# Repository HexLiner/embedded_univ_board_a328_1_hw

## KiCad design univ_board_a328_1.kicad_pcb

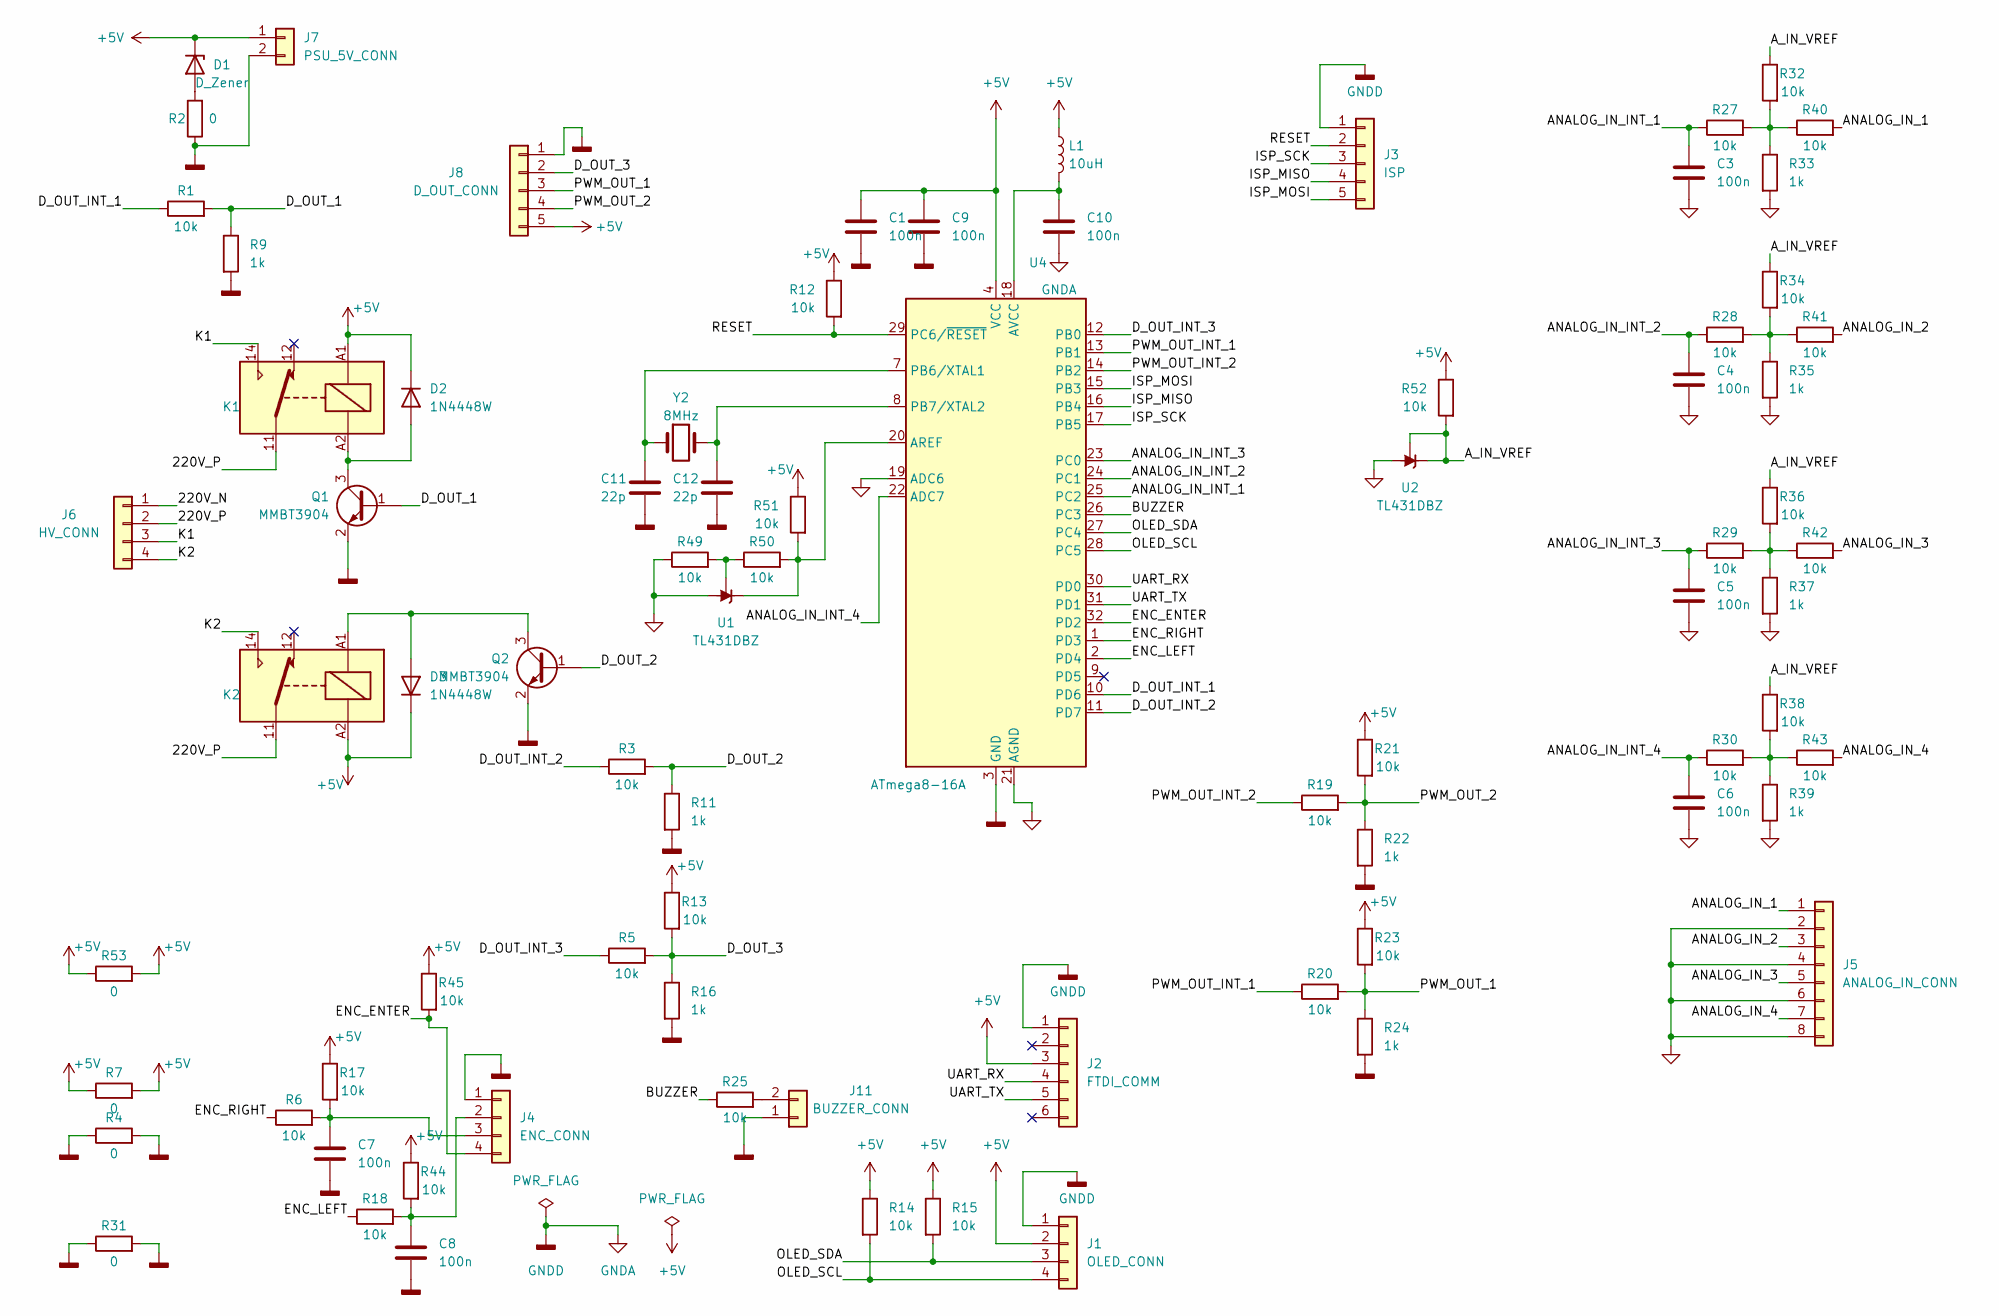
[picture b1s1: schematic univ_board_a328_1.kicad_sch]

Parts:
C1, C3, C4, C5, C6, C7, C8, C9, C10: 100n; C_0805_2012Metric
C11, C12: 22p; C_0603_1608Metric
D1: D_Zener; D_SOD-123
D2, D3: 1N4448W; D_SOD-123
J1: OLED_CONN; PinHeader_1x04_P2.54mm_Vertical
J2: FTDI_COMM; PinSocket_1x06_P2.54mm_Vertical
J3: ISP; PinSocket_1x05_P2.54mm_Vertical
J4: ENC_CONN; PinHeader_1x04_P2.54mm_Vertical
J5: ANALOG_IN_CONN; my_8pin_smd_conn
J6: HV_CONN; my_4pin_220v_conn
J7: PSU_5V_CONN; my_2pin_DIP_conn
J8: D_OUT_CONN; my_5pin_snd_conn
J11: BUZZER_CONN; PinHeader_1x02_P2.54mm_Vertical
K1, K2: FINDER-36.11; Relay_SPDT_Finder_36.11
L1: 10uH; L_0805_2012Metric
Q1, Q2: MMBT3904; SOT-23
R1, R3, R5, R6, R12, R14, R15, R18, R19, R20, R21, R25, R27, R28, R29, R30, R32, R34, R36, R38, R40, R41, R42, R43, R45, R49, R50, R51, R52: 10k; R_0805_2012Metric
R2, R4, R7, R31, R53: 0; R_1206_3216Metric
R9, R11, R16, R22, R24, R33, R35, R37, R39: 1k; R_0805_2012Metric
R13, R17, R23, R44: 10k; R_1206_3216Metric
U1, U2: TL431DBZ; SOT-23
U4: ATmega8-16A; TQFP-32_7x7mm_P0.8mm
Y2: 8MHz; Crystal_HC18-U_Vertical

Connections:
+5V: C1.1, C9.1, D1.1 (K), D2.1 (K), D3.1 (K), J1.2, J2.3, J7.1, J8.5, K1.A1, K2.A2, L1.1, R7.1, R7.2, R12.1, R13.1, R14.1, R15.1, R17.1, R21.1, R23.1, R44.1, R45.1, R51.1, R52.1, R53.1, R53.2, U4.4 (VCC), U4.6 (VCC)
/220V_N: J6.1
/220V_P: J6.2, K1.11, K2.11
/ANALOG_IN_1: J5.1, R40.2
/ANALOG_IN_2: J5.3, R41.2
/ANALOG_IN_3: J5.5, R42.2
/ANALOG_IN_4: J5.7, R43.2
/ANALOG_IN_INT_1: C3.1, R27.1, U4.25 (PC2)
/ANALOG_IN_INT_2: C4.1, R28.1, U4.24 (PC1)
/ANALOG_IN_INT_3: C5.1, R29.1, U4.23 (PC0)
/ANALOG_IN_INT_4: C6.1, R30.1, U4.22 (ADC7)
/A_IN_VREF: R32.1, R34.1, R36.1, R38.1, R52.2, U2.1 (K), U2.2 (REF)
/BUZZER: R25.1, U4.26 (PC3)
/D_OUT_1: Q1.1 (B), R1.2, R9.1
/D_OUT_2: Q2.1 (B), R3.2, R11.1
/D_OUT_3: J8.2, R5.2, R13.2, R16.1
/D_OUT_INT_1: R1.1, U4.10 (PD6)
/D_OUT_INT_2: R3.1, U4.11 (PD7)
/D_OUT_INT_3: R5.1, U4.12 (PB0)
/ENC_ENTER: J4.4, R45.2, U4.32 (PD2)
/ENC_LEFT: R18.1, U4.2 (PD4)
/ENC_RIGHT: R6.1, U4.1 (PD3)
/ISP_MISO: J3.4, U4.16 (PB4)
/ISP_MOSI: J3.5, U4.15 (PB3)
/ISP_SCK: J3.3, U4.17 (PB5)
/K1: J6.3, K1.14
/K2: J6.4, K2.14
/OLED_SCL: J1.4, R14.2, U4.28 (PC5)
/OLED_SDA: J1.3, R15.2, U4.27 (PC4)
/PWM_OUT_1: J8.3, R20.2, R23.2, R24.1
/PWM_OUT_2: J8.4, R19.2, R21.2, R22.1
/PWM_OUT_INT_1: R20.1, U4.13 (PB1)
/PWM_OUT_INT_2: R19.1, U4.14 (PB2)
/RESET: J3.2, R12.2, U4.29 (PC6/~RESET)
/UART_RX: J2.4, U4.30 (PD0)
/UART_TX: J2.5, U4.31 (PD1)
GNDA: C1.2, C3.2, C4.2, C5.2, C6.2, C7.2, C8.2, C9.2, C10.2, C11.2, C12.2, J1.1, J2.1, J3.1, J4.1, J5.2, J5.4, J5.6, J5.8, J7.2, J8.1, J11.1, Q1.2 (E), Q2.2 (E), R2.1, R4.1, R4.2, R9.2, R11.2, R16.2, R22.2, R24.2, R31.1, R31.2, R33.2, R35.2, R37.2, R39.2, R49.1, U1.3 (A), U2.3 (A), U4.3 (GND), U4.5 (GND), U4.19 (ADC6), U4.21 (AGND)
unnamed: C7.1, J4.3, R6.2, R17.2
unnamed: C8.1, J4.2, R18.2, R44.2
unnamed: C10.1, L1.2, U4.18 (AVCC)
unnamed: C11.1, U4.7 (PB6/XTAL1), Y2.1
unnamed: C12.1, U4.8 (PB7/XTAL2), Y2.2
unnamed: D1.2 (A), R2.2
unnamed: D2.2 (A), K1.A2, Q1.3 (C)
unnamed: D3.2 (A), K2.A1, Q2.3 (C)
unnamed: J11.2, R25.2
unnamed: R27.2, R32.2, R33.1, R40.1
unnamed: R28.2, R34.2, R35.1, R41.1
unnamed: R29.2, R36.2, R37.1, R42.1
unnamed: R30.2, R38.2, R39.1, R43.1
unnamed: R49.2, R50.1, U1.2 (REF)
unnamed: R50.2, R51.2, U1.1 (K), U4.20 (AREF)

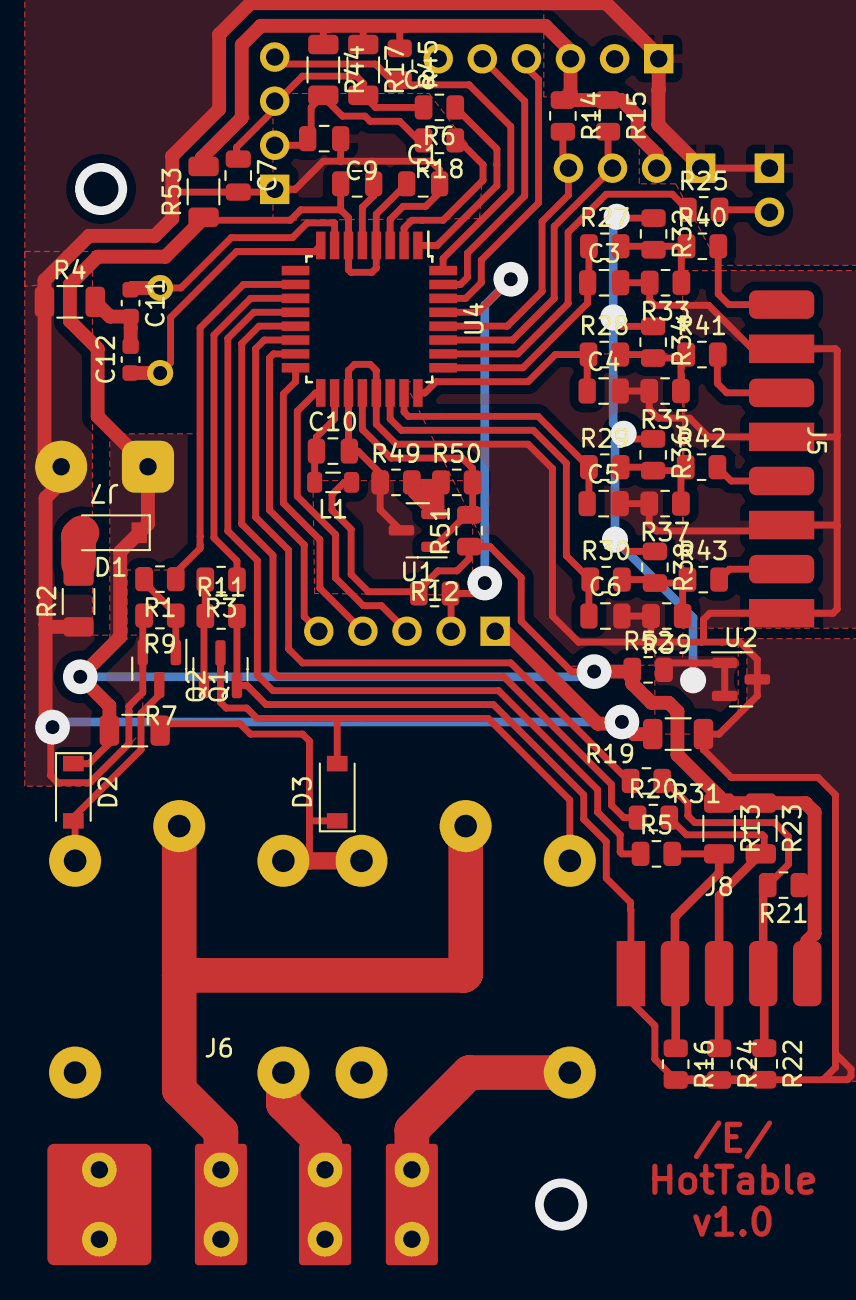
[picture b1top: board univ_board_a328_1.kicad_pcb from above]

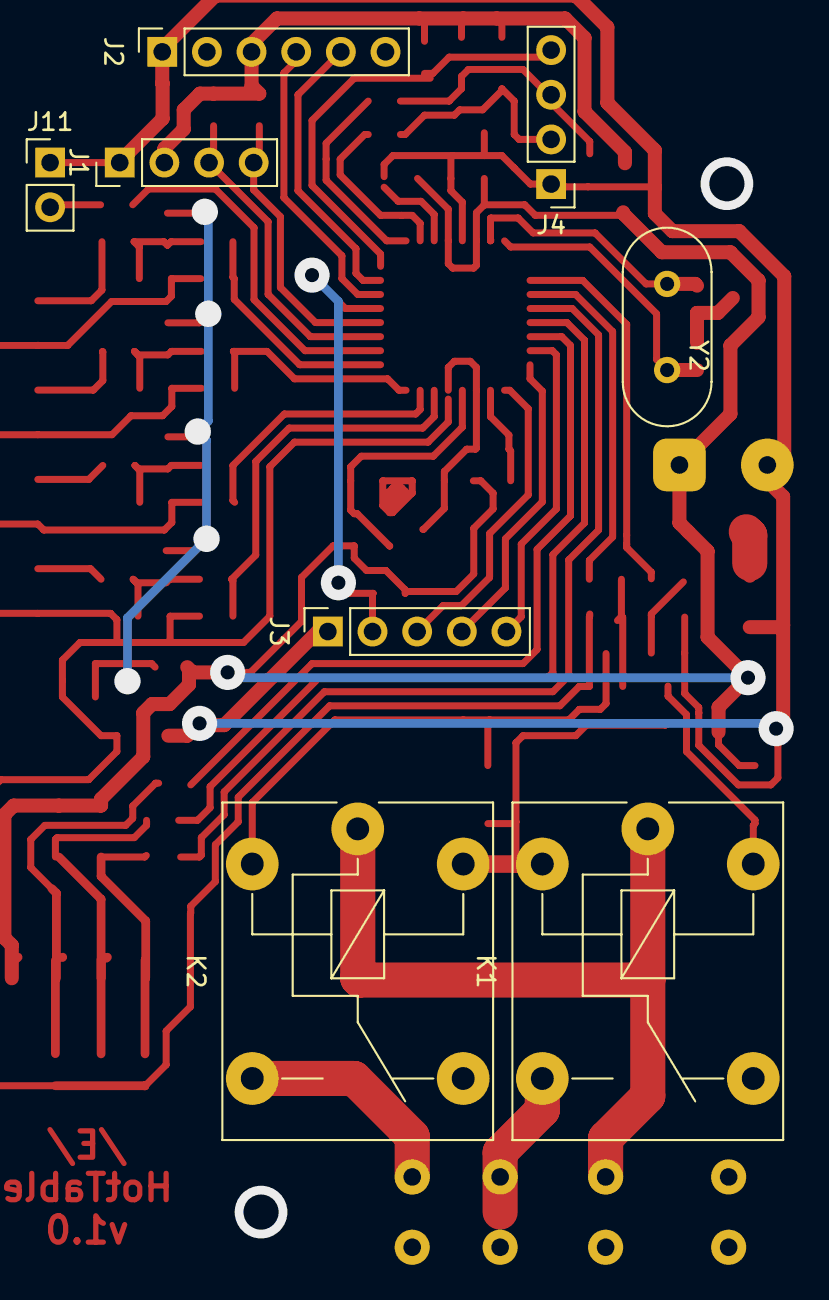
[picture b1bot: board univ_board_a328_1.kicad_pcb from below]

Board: 2 copper layers, 79 parts (8 on the bottom side), 51 nets.

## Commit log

2025-03-05 Initial
